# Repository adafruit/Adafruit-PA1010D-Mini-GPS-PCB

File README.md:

## Adafruit PA1010D Mini GPS Module PCB

<a href="http://www.adafruit.com/products/4415"><br/>
Click here to purchase one from the Adafruit shop</a>

PCB files for the Adafruit PA1010D Mini GPS Module. 

Format is EagleCAD schematic and board layout
* https://www.adafruit.com/product/4415

### Description

This miniature GPS breakout is only 1" x 1" (~ 25mm x 25mm) but houses a complete GPS/GNSS solution with both I2C and UART interfaces. There's even an antenna on top so it's plug and play!

* Support for GPS, GLONASS, GALILEO, QZSS
* -165 dBm sensitivity, up to 10 Hz updates
* Up to 210 PRN channels with 99 search channels and 33 simultaneous tracking channels
* 5V friendly design and only 30mA current draw
* Breadboard-able, with 4 mounting holes
* UART and I2C interfaces, pick whichever you like most!
* RTC battery-compatible
* PPS output on fix ±20ns jitter
* Internal patch antenna
* Low-power and standby mode with WAKE pin

The breakout is built around the MTK3333 chipset, a reliable, high-quality GPS module that can handle up to 33 simultaneous tracking channels, has an excellent high-sensitivity receiver (-165 dBm tracking!), and a built in antenna. It can do up to 10 location updates a second for high speed, high sensitivity logging or tracking. Power usage is incredibly low, only 30 mA during navigation.

Best of all, we added all the extra goodies you could ever want: a ultra-low dropout 3.3V regulator so you can power it with 3.3-5VDC in, 5V level safe inputs on UART and I2C, a footprint for optional CR1220 coin cell to keep the RTC running and allow warm starts, a green power LED and a tiny red PPS LED. The LED blinks at about 1Hz when a fix is found and is off when no fix.

Unlike our Ultimate GPS modules, this module does not have the ability to connect an external antenna, it's designed to be as small as possible for compact projects.

As with all Adafruit breakouts, we've done the work to make this GPS module super easy to use. We've put it on a breakout board with the required support circuitry and connectors to make it easy to work with, and is now a trend we've added SparkFun Qwiic compatible STEMMA QT JST SH connectors that allow you to get going without needing to solder. Just use a STEMMA QT adapter cable, plug it into your favorite micro or Blinka supported SBC and you're ready to rock!

Comes with one fully assembled and tested module, a piece of header you can solder to it for bread-boarding, and a CR1220 coin cell holder. A CR1220 coin cell is not included, but we have them in the shop if you'd like to use the GPS's RTC

We have a nice fancy library for GPS usage for both Arduino and Python usage. A full tutorial is also available, which has tons of information about the module, how to use the data logger, example code for both CircuitPython & Arduino, and more

### License

Adafruit invests time and resources providing this open source design, please support Adafruit and open-source hardware by purchasing products from [Adafruit](https://www.adafruit.com)!

Designed by Limor Fried/Ladyada for Adafruit Industries.

Creative Commons Attribution/Share-Alike, all text above must be included in any redistribution. 
See license.txt for additional details.

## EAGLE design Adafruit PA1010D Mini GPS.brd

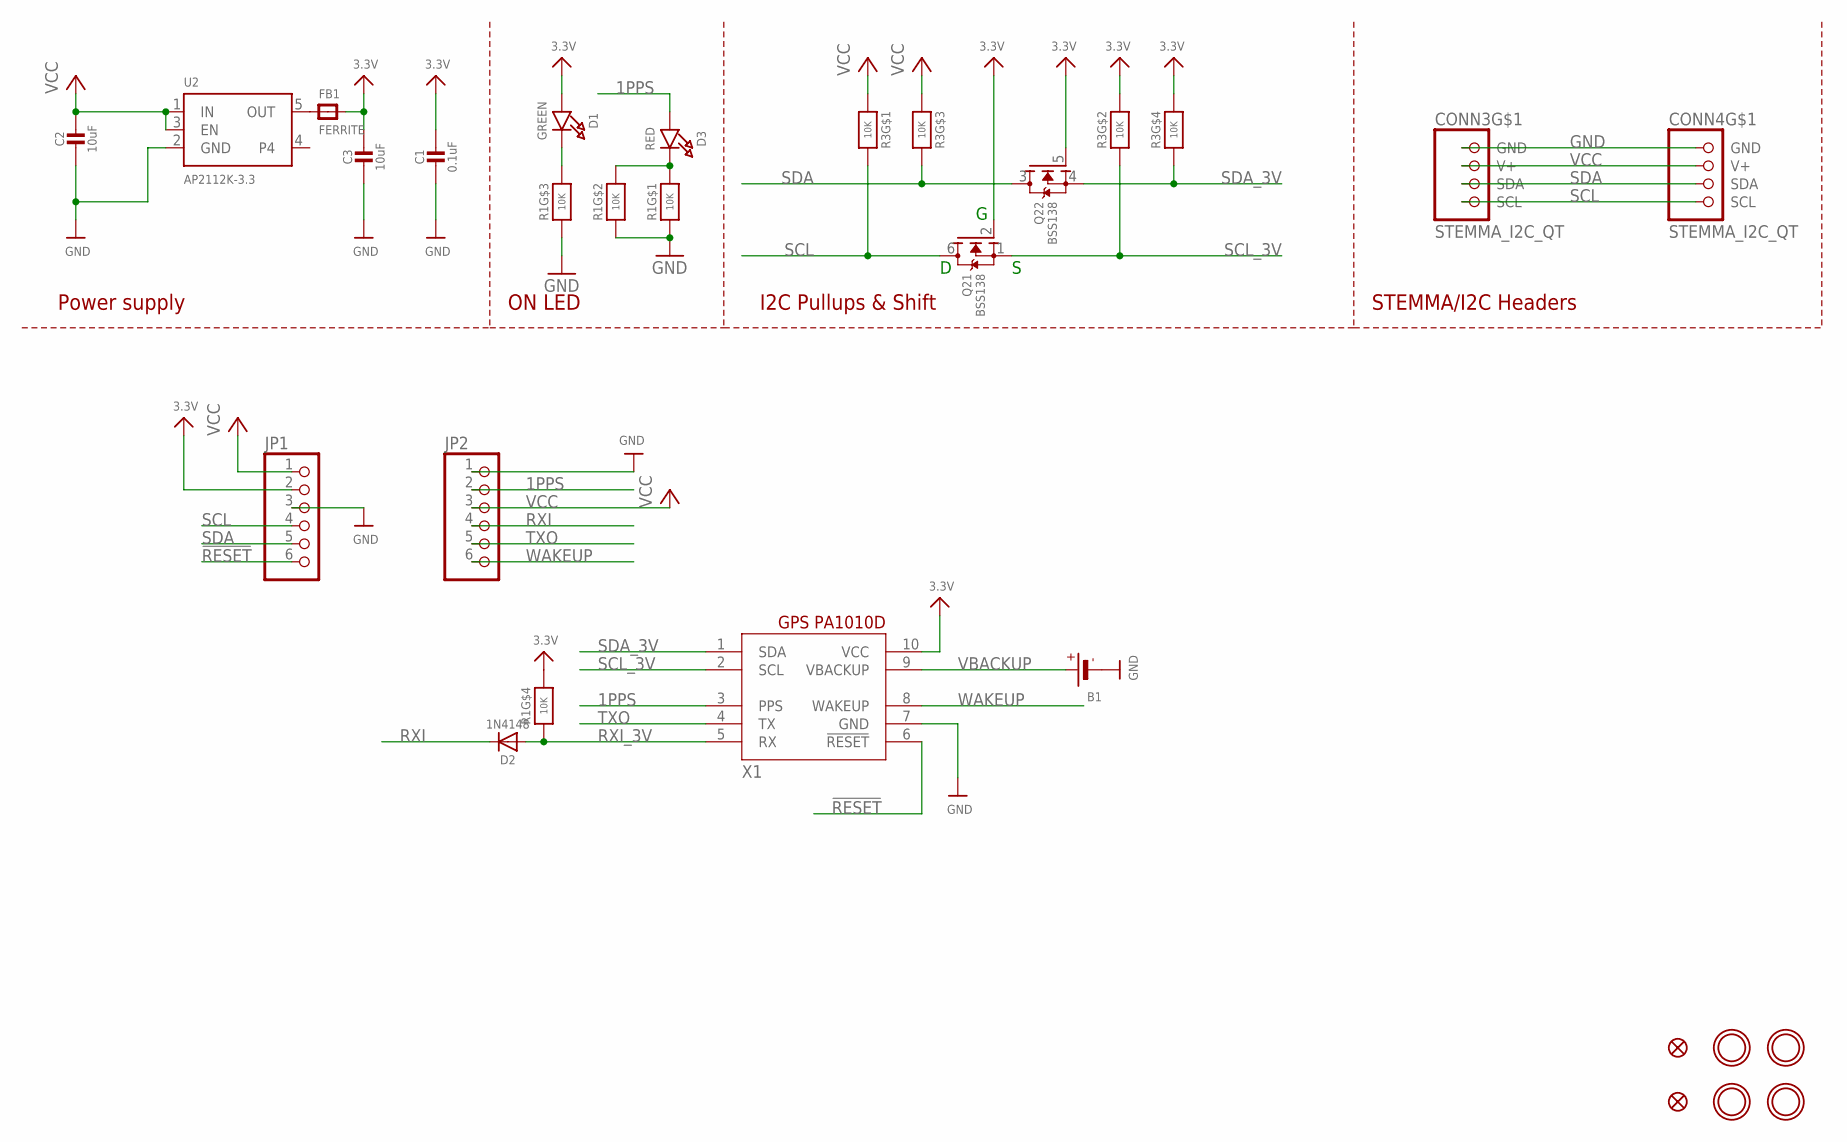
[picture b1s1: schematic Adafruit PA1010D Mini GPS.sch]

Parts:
B1: BATTERYCR1220_2; CR1220-2
C1: 0.1uF; 0603-NO
C2, C3: 10uF; 0805-NO
CONN3, CONN4: STEMMA_I2C_QT; JST_SH4
D1: GREEN; CHIPLED_0603_NOOUTLINE
D2: 1N4148; SOD-323
D3: RED; CHIPLED_0603_NOOUTLINE
FB1: FERRITE; 0805-NO
FID3, FID4: FIDUCIAL_1MM
JP1, JP2: HEADER-1X670MIL; 1X06_ROUND_70
Q2: BSS138; SOT363
R1, R3: 10K; RESPACK_4X0603
U2: AP2112K-3.3; SOT23-5
U$1, U$17, U$19, U$21: MOUNTINGHOLE2.5; MOUNTINGHOLE_2.5_PLATED
X1: GPS_PA1010D

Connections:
1PPS: D3.A, JP2.2, X1.3 (PPS)
3.3V: C1.1, C3.1, D1.A, FB1.2, JP1.2, Q2.2 (G), Q2.5 (G), R1.4 (1), R3.2 (1), R3.4 (1), X1.10 (VCC)
!RESET: JP1.6, X1.6 (!RESET)
GND: B1.-, C1.2, C2.2, C3.2, CONN3.1 (GND), CONN4.1 (GND), JP1.3, JP2.1, R1.1, R1.2 (1), R1.3 (1), U2.2 (GND), X1.7 (GND)
unnamed: D1.C, R1.6 (2)
unnamed: D3.C, R1.7 (2), R1.8 (2)
OUT: FB1.1, U2.5 (OUT)
RXI: D2.C, JP2.4
RXI_3V: D2.A, R1.5 (2), X1.5 (RX)
SCL: CONN3.4 (SCL), CONN4.4 (SCL), JP1.4, Q2.6 (D), R3.8 (2)
SCL_3V: Q2.1 (S), R3.7 (2), X1.2 (SCL)
SDA: CONN3.3 (SDA), CONN4.3 (SDA), JP1.5, Q2.3 (D), R3.6 (2)
SDA_3V: Q2.4 (S), R3.5 (2), X1.1 (SDA)
TXO: JP2.5, X1.4 (TX)
VBACKUP: B1.+, X1.9 (VBACKUP)
VCC: C2.1, CONN3.2 (V+), CONN4.2 (V+), JP1.1, JP2.3, R3.1, R3.3 (1), U2.1 (IN), U2.3 (EN)
WAKEUP: JP2.6, X1.8 (WAKEUP)

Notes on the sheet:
I2C Pullups & Shift
STEMMA/I2C Headers
ON LED
Power supply

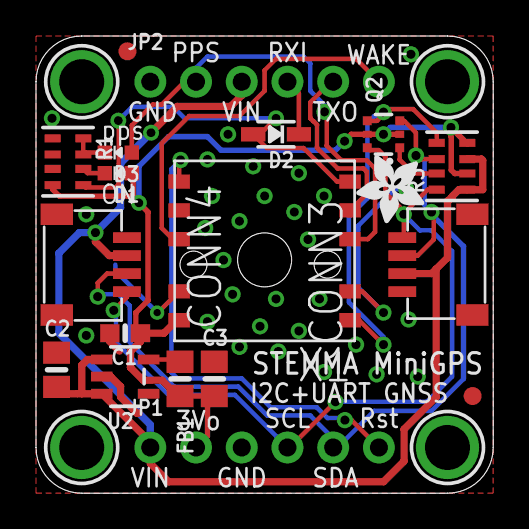
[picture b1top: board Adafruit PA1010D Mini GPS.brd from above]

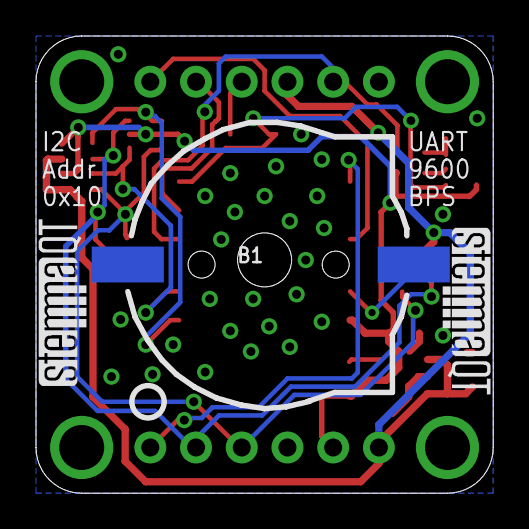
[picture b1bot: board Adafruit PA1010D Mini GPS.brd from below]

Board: 2 copper layers, 25.4 x 25.4 mm, 27 parts (4 on the bottom side), 17 nets.

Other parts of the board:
U$22: ADAFRUIT_3.5MM
U$25: PCBFEAT-REV-040
U$30, U$31: STEMMAQT

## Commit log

2019-11-15 Adding board files.

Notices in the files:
parts and their libraries:
microbuilder: This work is placed in the public domain, and may be freely used for commercial and non-commercial work with the following conditions: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
